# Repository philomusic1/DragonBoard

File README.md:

This is my keyboard inspired by the Corne Split Keyboard

It is a 58 Key Keyboard, with 2 Rotary encoders which have their switches wired into the Keyboard Switches matrix so it can be used as 60% keyboard

It is designed to be compatible with the Nice!Nano v2 and niceview display (the display can be swapped out for a oled one)

It is a reverisble PCB, so you only needs to send 1 gerber to your PCB manufacturer saving on costs and making it easier

The case is an acrylic case with a display protecter added

It is designed to be a wireless Keyboard with cherry mx hotswap switches with Per key RGB using SK6812 mini-e

Photos of the board follow Below:

Bottom Case:

Top Case:

Display Cover:

## BOM

| Name                             | Qty | Price (GBP)  |
| -------------------------------- | --- | -----------  |
| PCB                              | 1   | 08.89/w ship |
| Gateron G Pro 3.0 Silver         | 58  | 19.90/w ship (Mechmods) |
| Cherry mx switch sockets         | 58  | 02.46/70 (AE)       |
| SK6812MINI-E                     | 58  | 02.91/100pc (AE)    |
| Diodes 1N4148W SOD123            | 60  | 00.09/1pc (DigiKey) |
| 100nF 0402 capacitor             | 58  | 00.09/1pc (Digikey) |
| AO3401A Transistor               | 1   | 00.44/1pc (DigiKey) |
| 2N7002 Transistor                | 3   | 00.49/1pc (Digikey) |
| 100Ω 0402 resistor               | 1   | 00.09/1pc (Digikey) |
| 10kΩ 0402 resistor               | 2   | 00.09/1pc (Digikey) |
| buttons Momentary                | 2   | 00.22/1pc (Digikey) |
| 0.91" OLED SSD1306               | 2   | 03.16/2pc  (AE)     |
| Tenstar NRF52840 2pack           | 1   | 04.00/pack (AE)     |
| SPDT SMT slide switches          | 2   | 00.85/1pc (Digikey) |
| JST Headers                      | 2   | 00.09/1pc (Digikey) |
| JST Connector                    | 2   | 00.82/5pc  (AE)     |
| EC11 encoder                     | 2   | 02.46/5pc (Digikey) |
| EC11 knob                        | 2   | 01.07/5pc (Digikey) |
| Top Plate Acrylic                | 1   | Hack Club           |
| Bottom Plate Acrylic             | 1   | Hack Club           |
| OLED Acrylic                     | 1   | Hack Club           |
| M2 9mm Stand Offs                | 10  | 02.06/50   (AE)     |
| M2 12mm Stand Offs               | 4   | 02.15/50   (AE)     |
| M2 4mm screws                    | 28  | 00.92/50   (AE)     |
| 306080 LiPo Battery              | 2   | Not Sure whether its allowed (9.42/1pc) |
| KeyCaps                          | 1   | 14.03      (AE)     |
| Socket Kit (4 Sockets, 50 Millmax, 2 oled sockets) | 1   | 11.81  (mechboards) |

AE = AliExpress

| Name                             | Price (GBP) |
| -------------------------------- | ----------- |
| AliExpress                       | 35.93/w shipping (50.76 with batteries) |
| DigiKey                          | 24.02/w shipping |
| Mechmods                         | 19.90/w shipping |
| JLCPCB                           | 08.89/w shipping |
| Mechboards                       | 11.81/w shipping |
| -------------------------------- | ----------- |
| Total                            | 100.55 (115.38 with batteries) |

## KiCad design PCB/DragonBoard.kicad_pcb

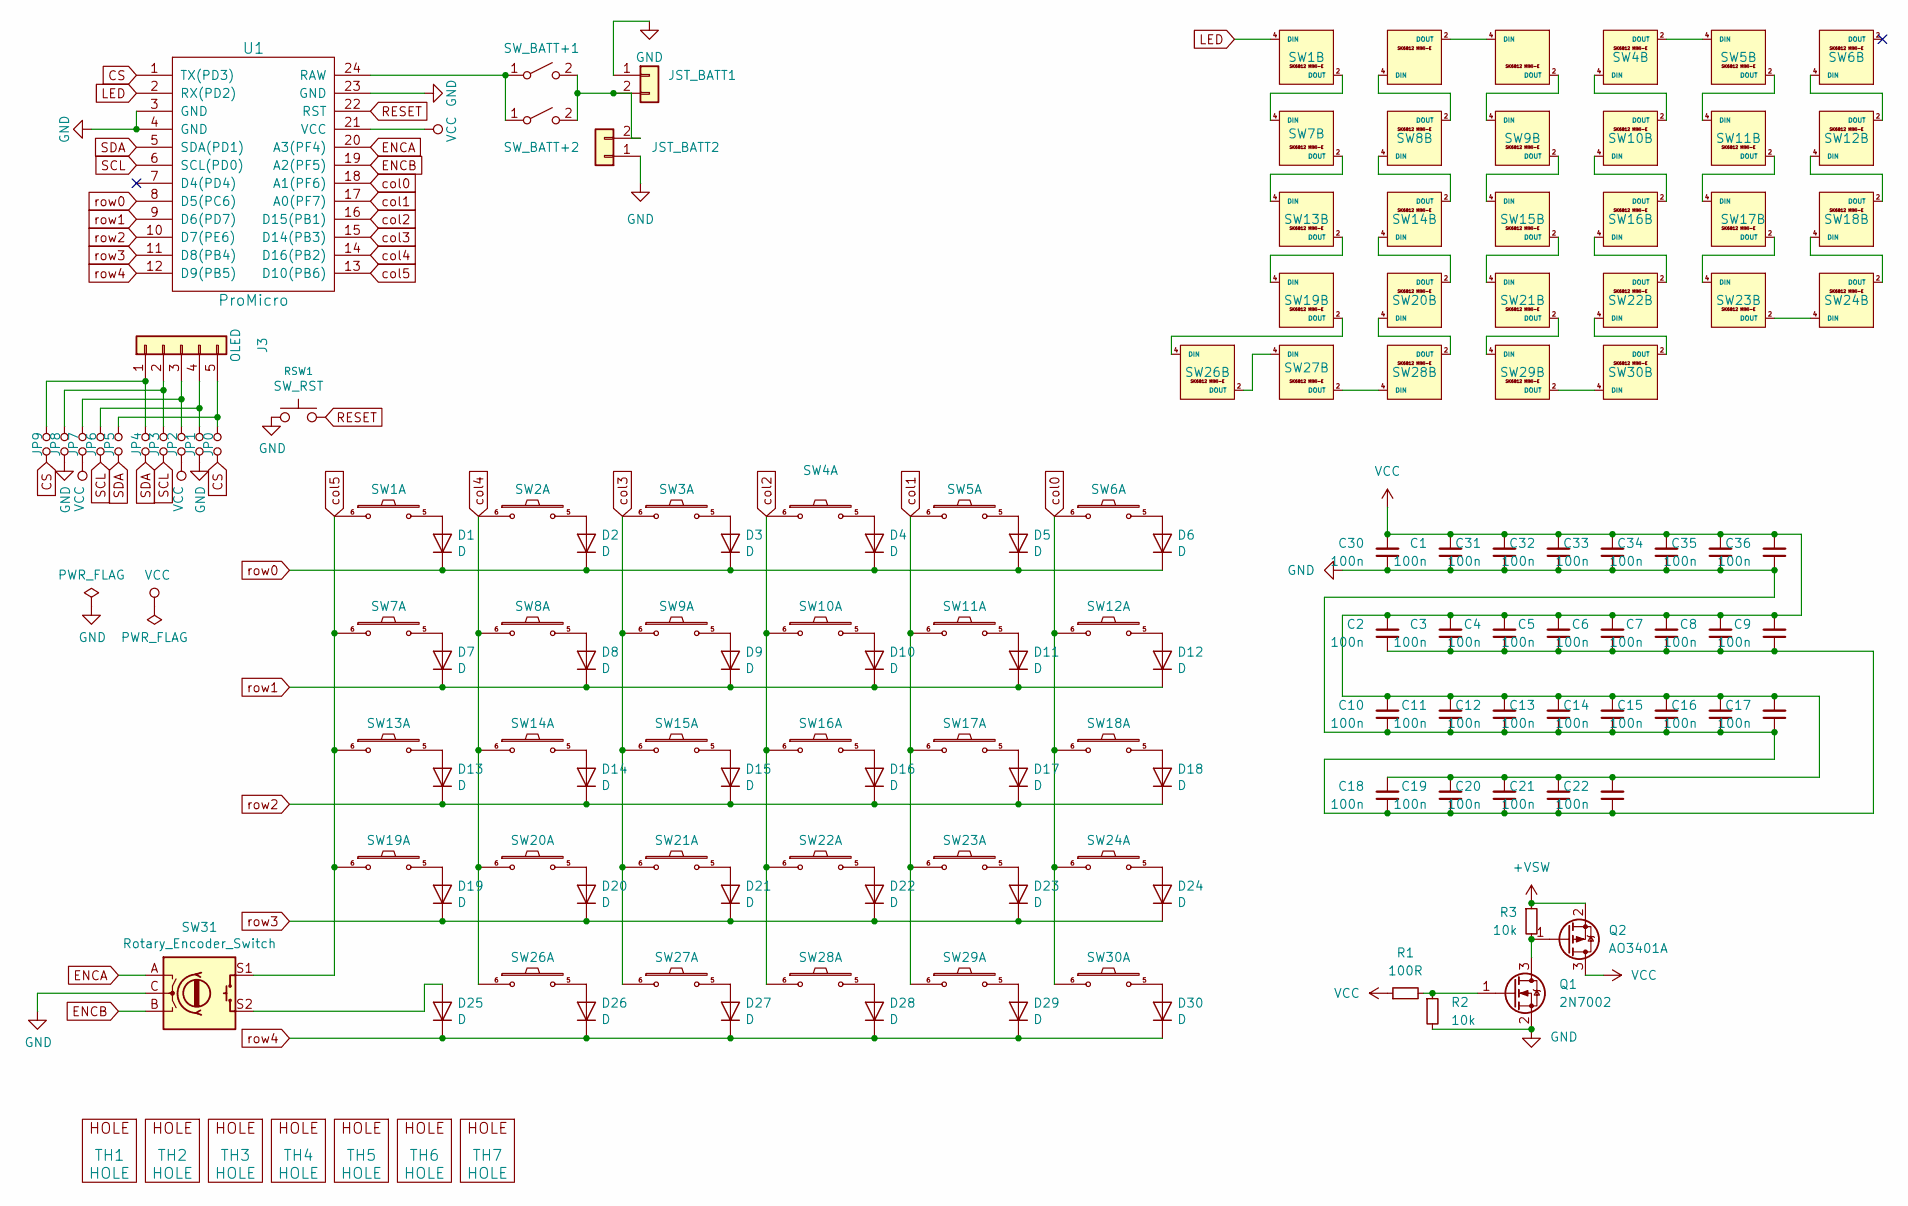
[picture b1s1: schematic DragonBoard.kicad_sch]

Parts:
C1, C2, C3, C4, C5, C6, C7, C8, C9, C10, C11, C12, C13, C14, C15, C16, C17, C18, C19, C20, C21, C22, C30, C31, C32, C33, C34, C35, C36: 100n; C_0402_1005Metric_Pad0.74x0.62mm_HandSolder
D1, D2, D3, D4, D5, D6, D7, D8, D9, D10, D11, D12, D13, D14, D15, D16, D17, D18, D19, D20, D21, D22, D23, D24, D25, D26, D27, D28, D29, D30: D; crkbd-diode
J3: OLED; OLED_NICEVIEW_COMBO_HDR_5Pin
JP0, JP1, JP2, JP3, JP4, JP5, JP6, JP7, JP8, JP9: Jumper_NO_Small; Jumper_small
JST_BATT1, JST_BATT2: Conn_01x02; JST_PH_S2B-PH-K_1x02_P2.00mm_DoubleSided
Q1: 2N7002; SOT-23
Q2: AO3401A; SOT-23
R1: 100R; R_0402_1005Metric_Pad0.72x0.64mm_HandSolder
R2, R3: 10k; R_0402_1005Metric_Pad0.72x0.64mm_HandSolder
RSW1: SW_RST; TACT_SWITCH_TVBP06
SW1, SW2, SW3, SW4, SW5, SW6, SW7, SW8, SW9, SW10, SW11, SW12, SW13, SW14, SW15, SW16, SW17, SW18, SW19, SW20, SW21, SW22, SW23, SW24, SW26, SW27, SW28, SW29, SW30: SW_PUSH_LED; SK6812MINI_and_cherry
SW31: Rotary_Encoder_Switch; RotaryEncoder_Alps_EC11E-Switch_Vertical_H20mm-keebio_modif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
SW_BATT+1, SW_BATT+2: SW_SPST; SW_SPDT_PCM12
TH1, TH2: HOLE; M2_HOLE_PCB
TH3, TH4, TH5, TH6, TH7: HOLE; HOLE_M2_TH
U1: ProMicro

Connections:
+VSW: Q2.2 (S), R3.1
CS: JP0.2, JP9.2, U1.1 (TX(PD3))
ENCA: SW31.A, U1.20 (A3(PF4))
ENCB: SW31.B, U1.19 (A2(PF5))
GND: C1.1, C2.1, C3.1, C4.1, C5.1, C6.1, C7.1, C8.1, C9.1, C10.1, C11.1, C12.1, C13.1, C14.1, C15.1, C16.1, C17.1, C18.1, C19.1, C20.1, C21.1, C22.1, C30.1, C31.1, C32.1, C33.1, C34.1, C35.1, C36.1, JP1.2, JP8.2, JST_BATT1.1, JST_BATT2.1, Q1.2 (S), R2.2, RSW1.1, SW1.3 (GND), SW2.3 (GND), SW3.3 (GND), SW4.3 (GND), SW5.3 (GND), SW6.3 (GND), SW7.3 (GND), SW8.3 (GND), SW9.3 (GND), SW10.3 (GND), SW11.3 (GND), SW12.3 (GND), SW13.3 (GND), SW14.3 (GND), SW15.3 (GND), SW16.3 (GND), SW17.3 (GND), SW18.3 (GND), SW19.3 (GND), SW20.3 (GND), SW21.3 (GND), SW22.3 (GND), SW23.3 (GND), SW24.3 (GND), SW26.3 (GND), SW27.3 (GND), SW28.3 (GND), SW29.3 (GND), SW30.3 (GND), SW31.C, U1.3 (GND), U1.4 (GND), U1.23 (GND)
LED: SW1.4 (DIN), U1.2 (RX(PD2))
unnamed: D1.2 (A), SW1.5
unnamed: D2.2 (A), SW2.5
unnamed: D3.2 (A), SW3.5
unnamed: D4.2 (A), SW4.5
unnamed: D5.2 (A), SW5.5
unnamed: D6.2 (A), SW6.5
unnamed: D7.2 (A), SW7.5
unnamed: D8.2 (A), SW8.5
unnamed: D9.2 (A), SW9.5
unnamed: D10.2 (A), SW10.5
unnamed: D11.2 (A), SW11.5
unnamed: D12.2 (A), SW12.5
unnamed: D13.2 (A), SW13.5
unnamed: D14.2 (A), SW14.5
unnamed: D15.2 (A), SW15.5
unnamed: D16.2 (A), SW16.5
unnamed: D17.2 (A), SW17.5
unnamed: D18.2 (A), SW18.5
unnamed: D19.2 (A), SW19.5
unnamed: D20.2 (A), SW20.5
unnamed: D21.2 (A), SW21.5
unnamed: D22.2 (A), SW22.5
unnamed: D23.2 (A), SW23.5
unnamed: D24.2 (A), SW24.5
unnamed: D25.2 (A), SW31.S2
unnamed: D26.2 (A), SW26.5
unnamed: D27.2 (A), SW27.5
unnamed: D28.2 (A), SW28.5
unnamed: D29.2 (A), SW29.5
unnamed: D30.2 (A), SW30.5
unnamed: J3.1, JP4.1, JP9.1
unnamed: J3.2, JP3.1, JP8.1
unnamed: J3.3, JP2.1, JP7.1
unnamed: J3.4, JP1.1, JP6.1
unnamed: J3.5, JP0.1, JP5.1
unnamed: JST_BATT1.2, JST_BATT2.2, SW_BATT+1.2 (B), SW_BATT+2.2 (B)
unnamed: Q1.3 (D), Q2.1 (G), R3.2
unnamed: Q1.1 (G), R1.2, R2.1
unnamed: SW1.2 (DOUT), SW7.4 (DIN)
unnamed: SW2.4 (DIN), SW8.2 (DOUT)
unnamed: SW2.2 (DOUT), SW3.4 (DIN)
unnamed: SW3.2 (DOUT), SW9.4 (DIN)
unnamed: SW4.2 (DOUT), SW5.4 (DIN)
unnamed: SW10.4 (DIN), SW16.2 (DOUT)
unnamed: SW4.4 (DIN), SW10.2 (DOUT)
unnamed: SW5.2 (DOUT), SW11.4 (DIN)
unnamed: SW11.2 (DOUT), SW17.4 (DIN)
unnamed: SW12.4 (DIN), SW18.2 (DOUT)
unnamed: SW6.4 (DIN), SW12.2 (DOUT)
unnamed: SW7.2 (DOUT), SW13.4 (DIN)
unnamed: SW13.2 (DOUT), SW19.4 (DIN)
unnamed: SW14.4 (DIN), SW20.2 (DOUT)
unnamed: SW8.4 (DIN), SW14.2 (DOUT)
unnamed: SW9.2 (DOUT), SW15.4 (DIN)
unnamed: SW15.2 (DOUT), SW21.4 (DIN)
unnamed: SW16.4 (DIN), SW22.2 (DOUT)
unnamed: SW17.2 (DOUT), SW23.4 (DIN)
unnamed: SW18.4 (DIN), SW24.2 (DOUT)
unnamed: SW19.2 (DOUT), SW26.4 (DIN)
unnamed: SW20.4 (DIN), SW28.2 (DOUT)
unnamed: SW21.2 (DOUT), SW29.4 (DIN)
unnamed: SW22.4 (DIN), SW30.2 (DOUT)
unnamed: SW23.2 (DOUT), SW24.4 (DIN)
unnamed: SW26.2 (DOUT), SW27.4 (DIN)
unnamed: SW27.2 (DOUT), SW28.4 (DIN)
unnamed: SW29.2 (DOUT), SW30.4 (DIN)
unnamed: SW_BATT+1.1 (A), SW_BATT+2.1 (A), U1.24 (RAW)
RESET: RSW1.2, U1.22 (RST)
SCL: JP3.2, JP6.2, U1.6 (SCL(PD0))
SDA: JP4.2, JP5.2, U1.5 (SDA(PD1))
VCC: C1.2, C2.2, C3.2, C4.2, C5.2, C6.2, C7.2, C8.2, C9.2, C10.2, C11.2, C12.2, C13.2, C14.2, C15.2, C16.2, C17.2, C18.2, C19.2, C20.2, C21.2, C22.2, C30.2, C31.2, C32.2, C33.2, C34.2, C35.2, C36.2, JP2.2, JP7.2, Q2.3 (D), R1.1, SW1.1 (VCC), SW2.1 (VCC), SW3.1 (VCC), SW4.1 (VCC), SW5.1 (VCC), SW6.1 (VCC), SW7.1 (VCC), SW8.1 (VCC), SW9.1 (VCC), SW10.1 (VCC), SW11.1 (VCC), SW12.1 (VCC), SW13.1 (VCC), SW14.1 (VCC), SW15.1 (VCC), SW16.1 (VCC), SW17.1 (VCC), SW18.1 (VCC), SW19.1 (VCC), SW20.1 (VCC), SW21.1 (VCC), SW22.1 (VCC), SW23.1 (VCC), SW24.1 (VCC), SW26.1 (VCC), SW27.1 (VCC), SW28.1 (VCC), SW29.1 (VCC), SW30.1 (VCC), U1.21 (VCC)
col0: SW6.6, SW12.6, SW18.6, SW24.6, SW30.6, U1.18 (A1(PF6))
col1: SW5.6, SW11.6, SW17.6, SW23.6, SW29.6, U1.17 (A0(PF7))
col2: SW4.6, SW10.6, SW16.6, SW22.6, SW28.6, U1.16 (D15(PB1))
col3: SW3.6, SW9.6, SW15.6, SW21.6, SW27.6, U1.15 (D14(PB3))
col4: SW2.6, SW8.6, SW14.6, SW20.6, SW26.6, U1.14 (D16(PB2))
col5: SW1.6, SW7.6, SW13.6, SW19.6, SW31.S1, U1.13 (D10(PB6))
row0: D1.1 (K), D2.1 (K), D3.1 (K), D4.1 (K), D5.1 (K), D6.1 (K), U1.8 (D5(PC6))
row1: D7.1 (K), D8.1 (K), D9.1 (K), D10.1 (K), D11.1 (K), D12.1 (K), U1.9 (D6(PD7))
row2: D13.1 (K), D14.1 (K), D15.1 (K), D16.1 (K), D17.1 (K), D18.1 (K), U1.10 (D7(PE6))
row3: D19.1 (K), D20.1 (K), D21.1 (K), D22.1 (K), D23.1 (K), D24.1 (K), U1.11 (D8(PB4))
row4: D25.1 (K), D26.1 (K), D27.1 (K), D28.1 (K), D29.1 (K), D30.1 (K), U1.12 (D9(PB5))

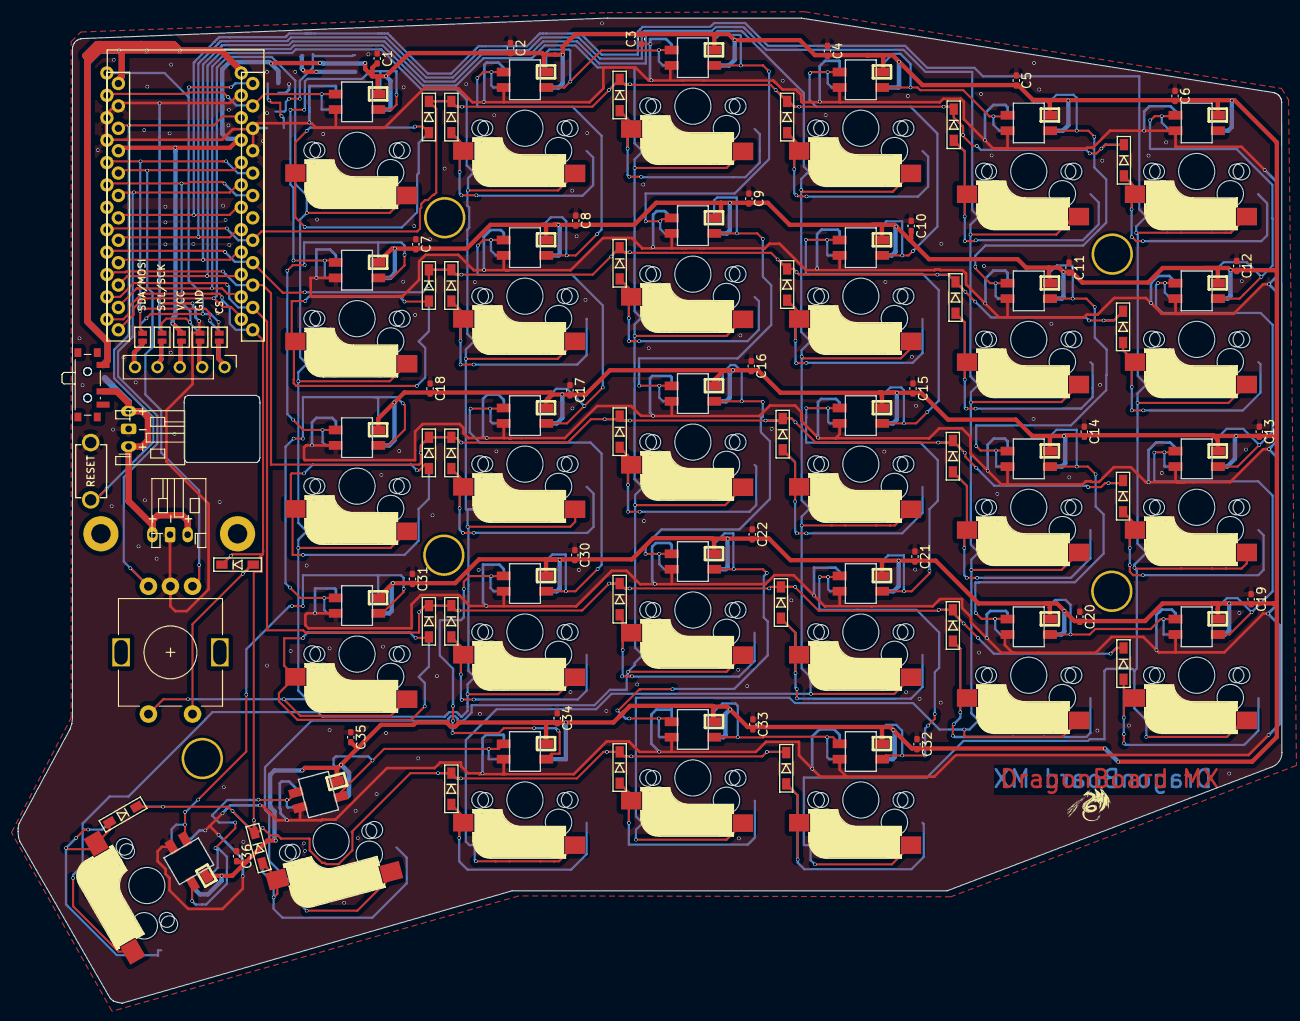
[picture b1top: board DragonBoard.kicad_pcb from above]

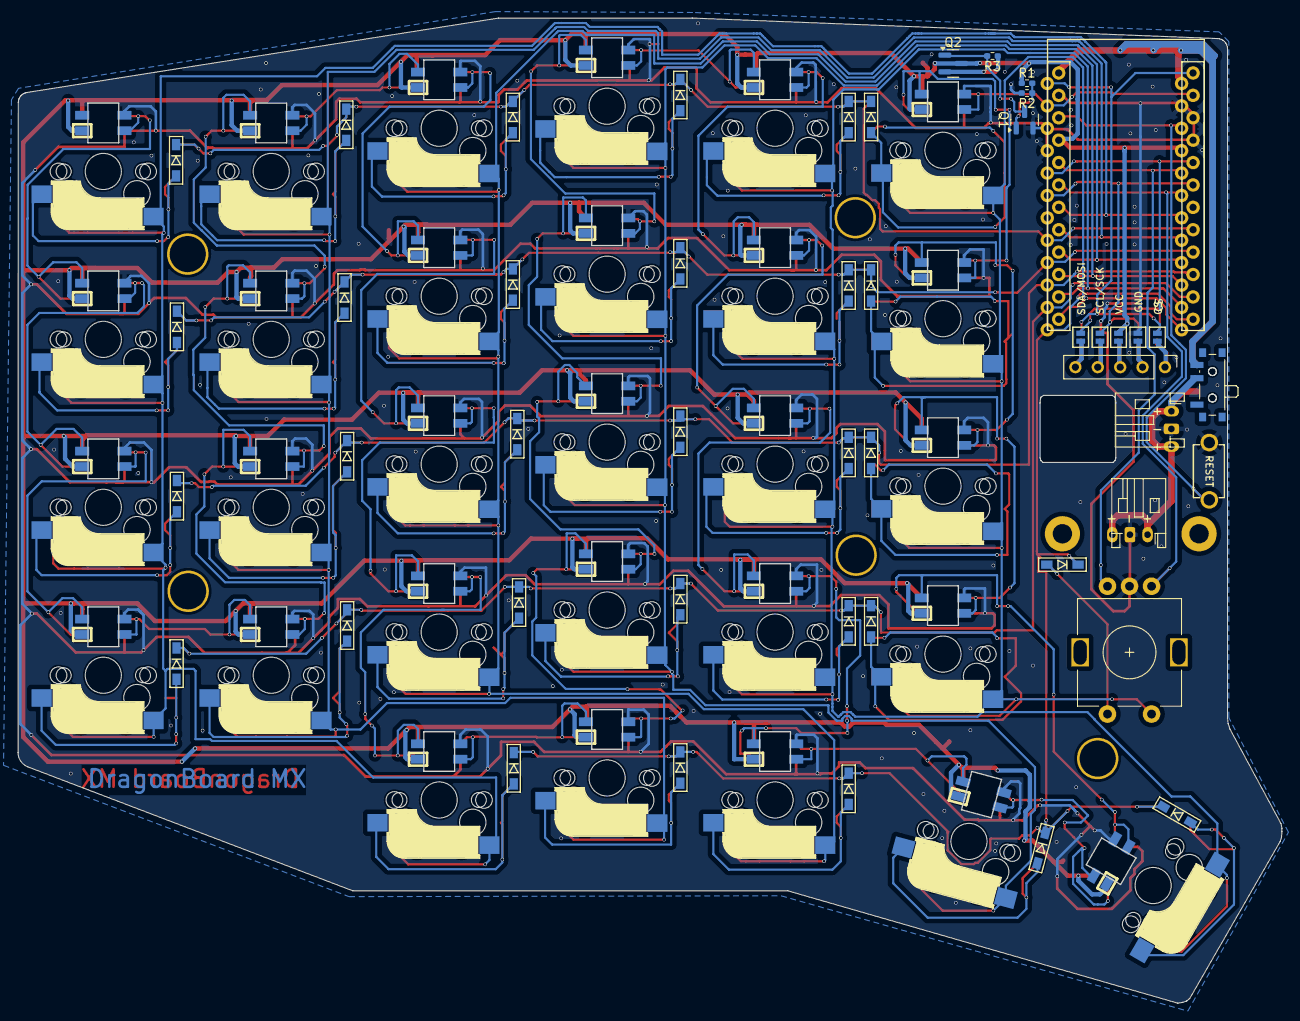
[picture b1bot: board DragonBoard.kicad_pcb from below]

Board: 2 copper layers, 143.4 x 111.8 mm, 118 parts (11 on the bottom side), 88 nets.

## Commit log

2025-02-26 initial repo
2025-02-26 update BoM
2025-03-01 update pcb and gerber to latest
2025-03-01 update pricing of BoM
2025-03-01 add missing sockets
2025-03-01 clarify socket kit
2025-03-01 fix the JLCDFM errors
2025-03-01 fix further JLCDFM errors
2025-03-01 fix remaining DFM checks
